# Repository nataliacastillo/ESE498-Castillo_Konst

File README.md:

# ESE498-Castillo_Konst
Capstone Project

This is the GitHub page for the 2021 ESE Capstone Design Project conducted by Natalia Castillo and Meagan Konst.<br/>
This project was titled "General Purpose Raspberry Pi HAT".<br/>
The report for this project can be found here: https://docs.google.com/document/d/1kZzHBrRYgLwNy8D9SOFyj6g7AGgq-kcxrAEOaCpLlvI/edit?usp=sharing<br/>
The final presentation slides can be found here: https://docs.google.com/presentation/d/1hZ809Xozr-wZa8N5Z7yGZ-oRJfP1h2XjGNVi-NlqP-0/edit?usp=sharing<br/>
The corresponding website can be found here: sites.wustl.edu/picap2021/<br/>

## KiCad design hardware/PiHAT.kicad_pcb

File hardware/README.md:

This section includes all of the KiCAD files for our PCB.

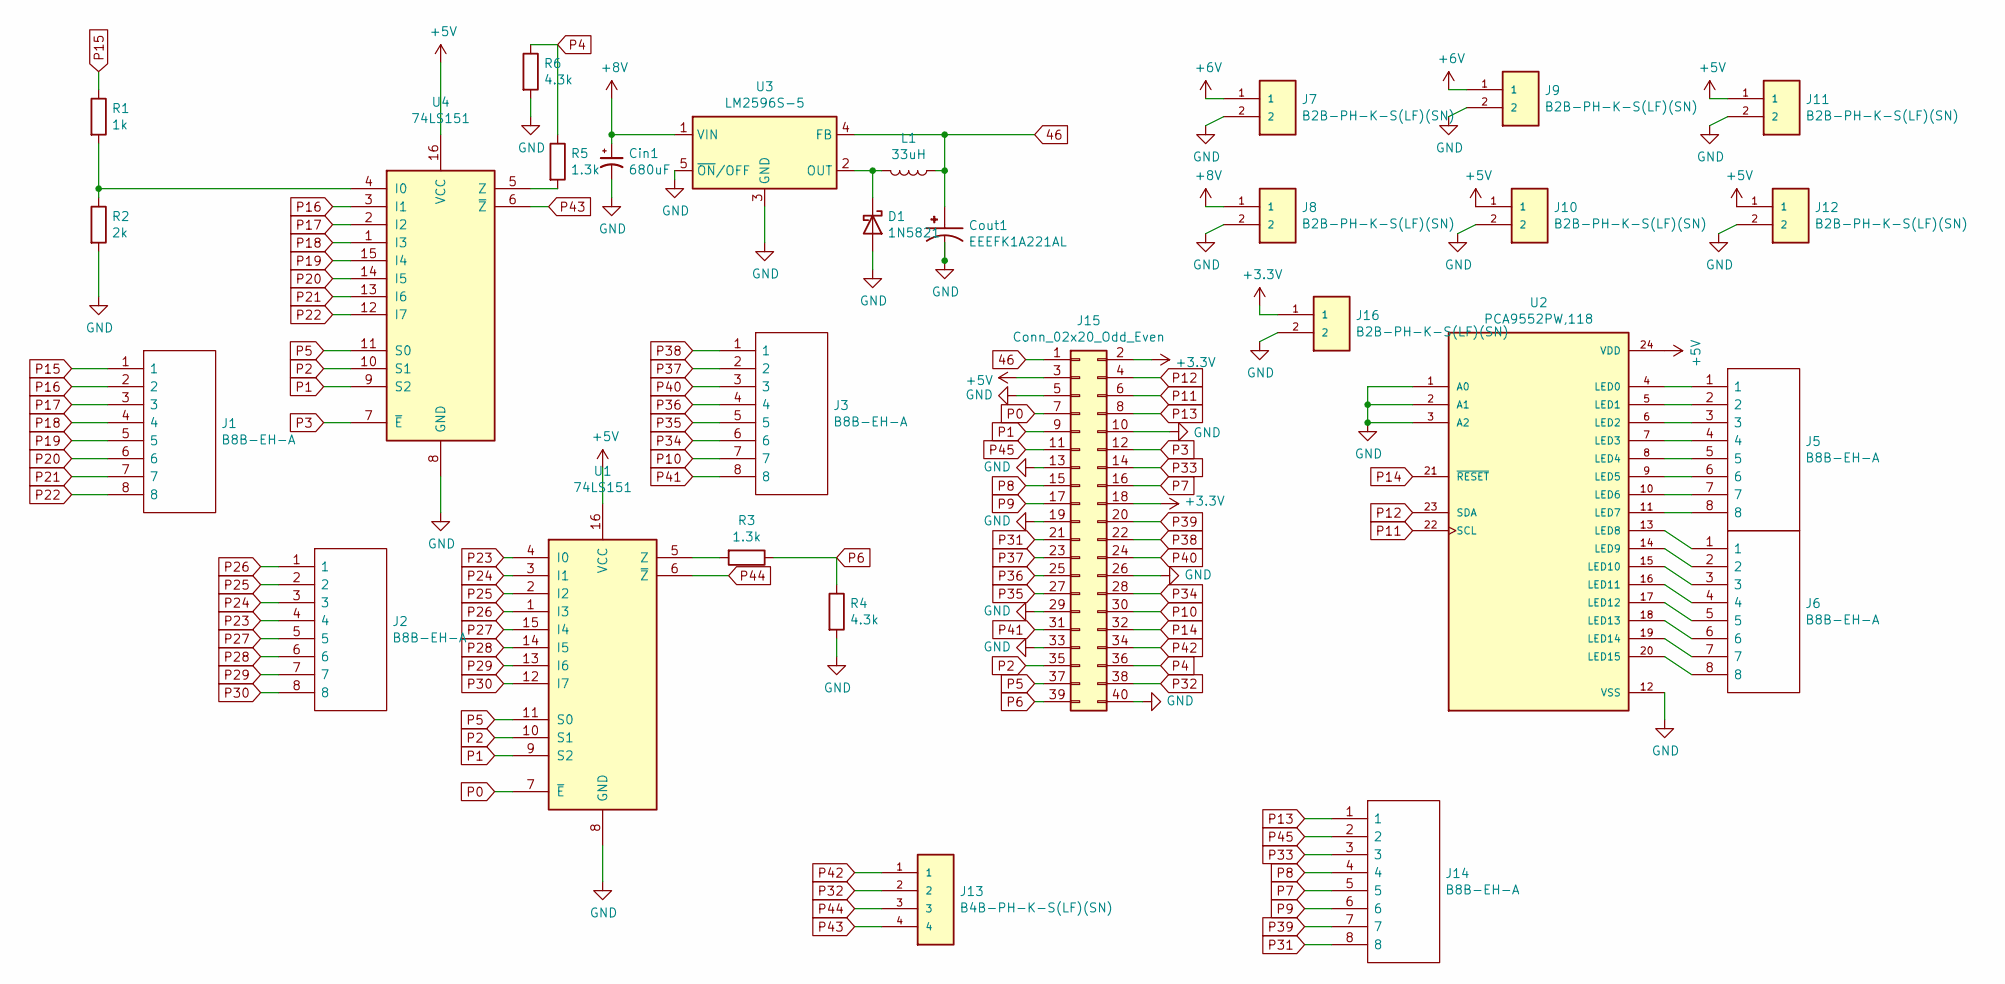
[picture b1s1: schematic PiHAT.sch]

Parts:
Cin1: 680uF; CP_Elec_10x10.5
Cout1: EEEFK1A221AL; CAP_EEEFK1A221AL; PARTREV 10-Oct-19
D1: 1N5821; D_DO-201AD_P15.24mm_Horizontal
J1, J2, J3, J5, J6, J14: B8B-EH-A; SHDR8W64P0X250_1X8_2250X380X600P; Manufacturer_Part_Number B8B-EH-A
J7, J8, J9, J10, J11, J12, J16: B2B-PH-K-S(LF)(SN); JST_B2B-PH-K-S(LF)(SN); PARTREV N/A; DIGI-KEY_PART_NUMBER 455-1704-ND
J13: B4B-PH-K-S(LF)(SN); JST_B4B-PH-K-S(LF)(SN)
J15: Conn_02x20_Odd_Even; Pin_Header_Straight_2x20
L1: 33uH; L_12x12mm_H8mm
R1: 1k; R_0402_1005Metric
R2: 2k; R_0402_1005Metric
R3, R5: 1.3k; R_0402_1005Metric
R4, R6: 4.3k; R_0402_1005Metric
U1, U4: 74LS151; SOIC127P600X175-16N
U2: PCA9552PW,118; SOP65P640X110-24N; PARTREV 05
U3: LM2596S-5; TO-263-5_TabPin3

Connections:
46: Cout1.1, J15.1, L1.1, U3.4 (FB)
+3V3: J15.2, J15.18, J16.1
+5V: J10.1, J11.1, J12.1, J15.3, U1.16 (VCC), U2.24 (VDD), U4.16 (VCC)
+6V: J7.1, J9.1
+8V: Cin1.1, J8.1, U3.1 (VIN)
GND: Cin1.2, Cout1.2, D1.2 (A), J7.2, J8.2, J9.2, J10.2, J11.2, J12.2, J15.5, J15.10, J15.13, J15.19, J15.26, J15.29, J15.33, J15.40, J16.2, R2.2, R4.2, R6.2, U1.8 (GND), U2.1 (A0), U2.2 (A1), U2.3 (A2), U2.12 (VSS), U3.3 (GND), U3.5 (~ON~/OFF), U4.8 (GND)
unnamed: D1.1 (K), L1.2, U3.2 (OUT)
unnamed: J5.1, U2.4 (LED0)
unnamed: J5.2, U2.5 (LED1)
unnamed: J5.3, U2.6 (LED2)
unnamed: J5.4, U2.7 (LED3)
unnamed: J5.5, U2.8 (LED4)
unnamed: J5.6, U2.9 (LED5)
unnamed: J5.7, U2.10 (LED6)
unnamed: J5.8, U2.11 (LED7)
unnamed: J6.1, U2.13 (LED8)
unnamed: J6.2, U2.14 (LED9)
unnamed: J6.3, U2.15 (LED10)
unnamed: J6.4, U2.16 (LED11)
unnamed: J6.5, U2.17 (LED12)
unnamed: J6.6, U2.18 (LED13)
unnamed: J6.7, U2.19 (LED14)
unnamed: J6.8, U2.20 (LED15)
unnamed: R1.2, R2.1, U4.4 (I0)
unnamed: R3.2, U1.5 (Z)
unnamed: R5.2, U4.5 (Z)
P0: J15.7, U1.7 (~E)
P1: J15.9, U1.9 (S2), U4.9 (S2)
P2: J15.35, U1.10 (S1), U4.10 (S1)
P3: J15.12, U4.7 (~E)
P4: J15.36, R5.1, R6.1
P5: J15.37, U1.11 (S0), U4.11 (S0)
P6: J15.39, R3.1, R4.1
P7: J14.5, J15.16
P8: J14.4, J15.15
P9: J14.6, J15.17
P10: J3.7, J15.30
P11: J15.6, U2.22 (SCL)
P12: J15.4, U2.23 (SDA)
P13: J14.1, J15.8
P14: J15.32, U2.21 (~RESET)
P15: J1.1, R1.1
P16: J1.2, U4.3 (I1)
P17: J1.3, U4.2 (I2)
P18: J1.4, U4.1 (I3)
P19: J1.5, U4.15 (I4)
P20: J1.6, U4.14 (I5)
P21: J1.7, U4.13 (I6)
P22: J1.8, U4.12 (I7)
P23: J2.4, U1.4 (I0)
P24: J2.3, U1.3 (I1)
P25: J2.2, U1.2 (I2)
P26: J2.1, U1.1 (I3)
P27: J2.5, U1.15 (I4)
P28: J2.6, U1.14 (I5)
P29: J2.7, U1.13 (I6)
P30: J2.8, U1.12 (I7)
P31: J14.8, J15.21
P32: J13.2, J15.38
P33: J14.3, J15.14
P34: J3.6, J15.28
P35: J3.5, J15.27
P36: J3.4, J15.25
P37: J3.2, J15.23
P38: J3.1, J15.22
P39: J14.7, J15.20
P40: J3.3, J15.24
P41: J3.8, J15.31
P42: J13.1, J15.34
P43: J13.4, U4.6 (~Z)
P44: J13.3, U1.6 (~Z)
P45: J14.2, J15.11

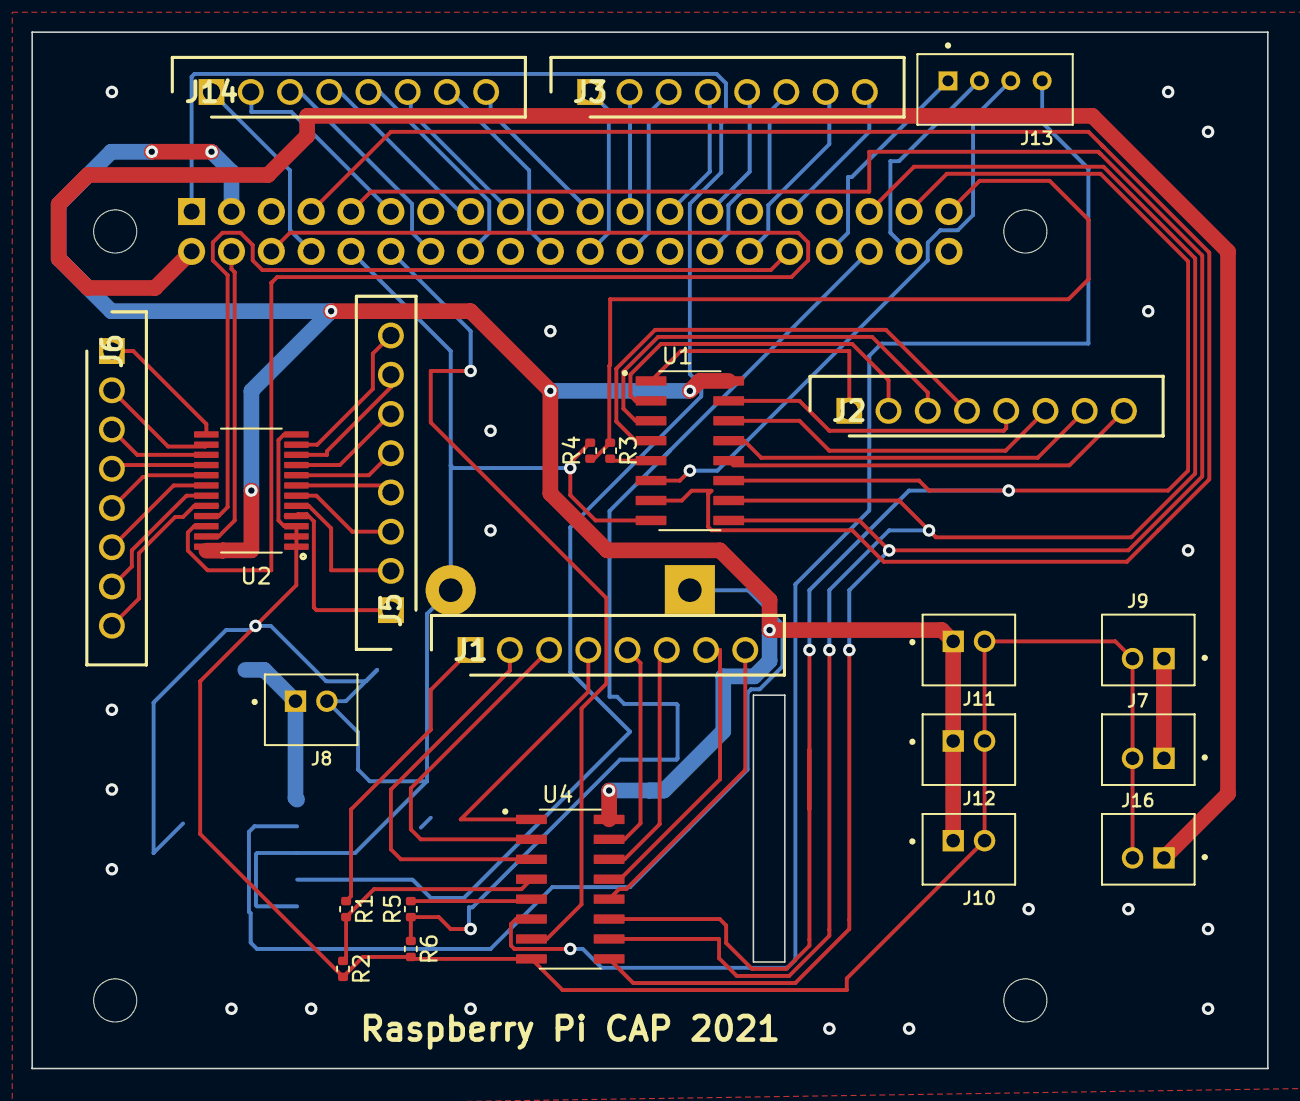
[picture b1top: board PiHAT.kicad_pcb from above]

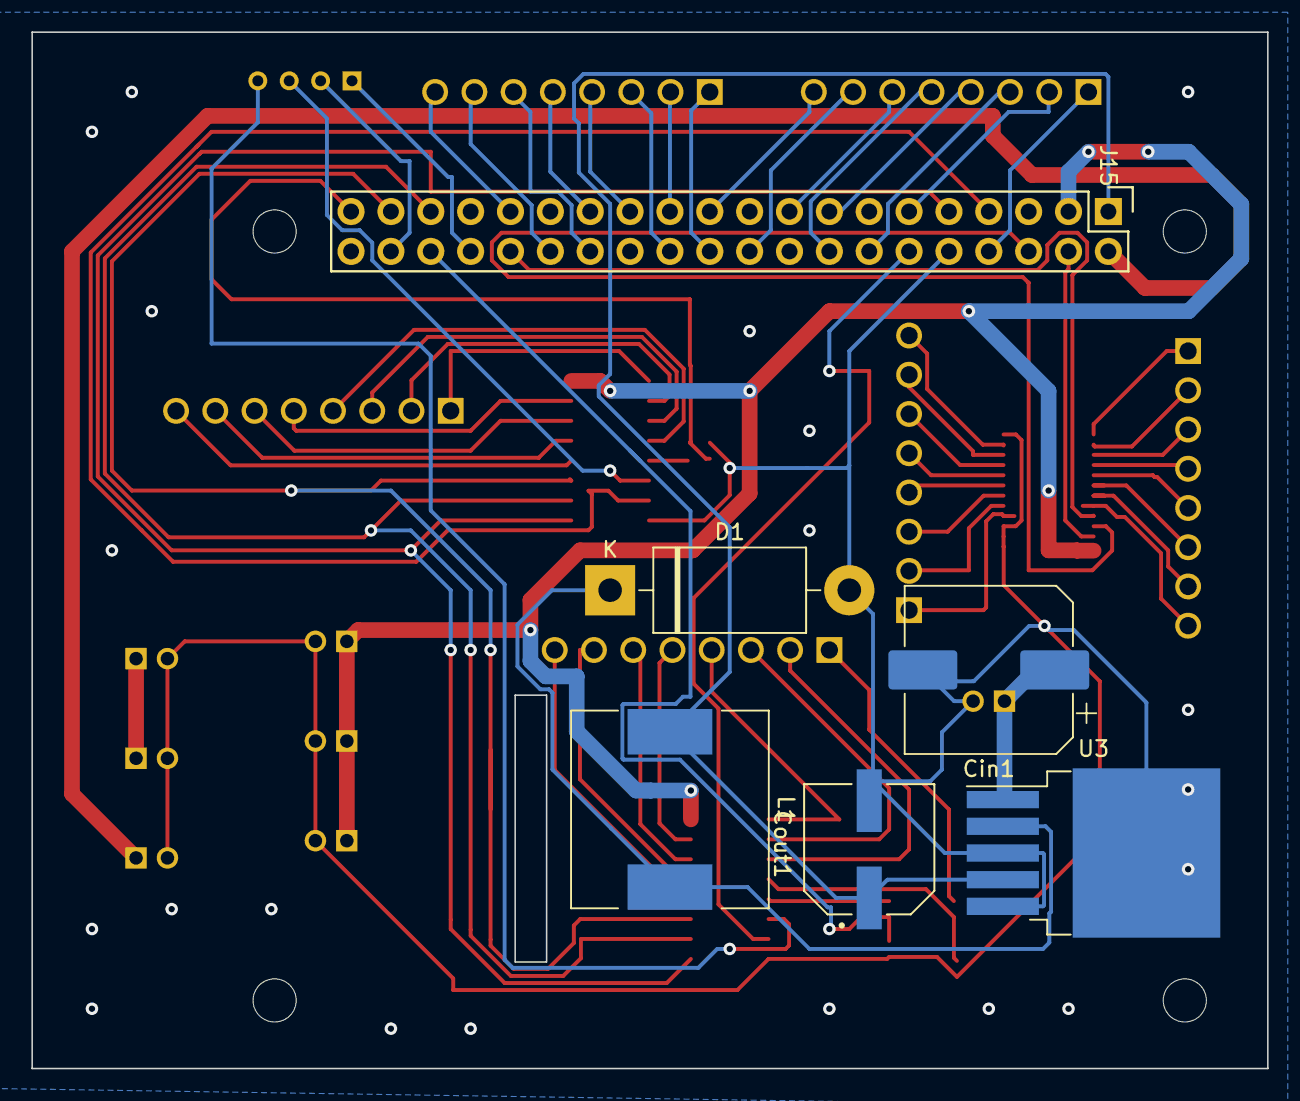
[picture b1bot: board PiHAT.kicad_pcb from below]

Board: 2 copper layers, 78.7 x 66.0 mm, 29 parts (6 on the bottom side), 72 nets.

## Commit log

2021-10-19 Add files via upload
    Rough draft of PiHAT schematic
2021-10-26 Create DW COMMENT
2021-12-17 Rename PiHAT-cache.lib to hardware/PiHAT-cache.lib
2021-12-17 Rename PiHAT.kicad_pcb to hardware/PiHAT.kicad_pcb
2021-12-17 Rename PiHAT.kicad_pcb-bak to hardware/PiHAT.kicad_pcb-bak
2021-12-17 Rename PiHAT.net to hardware/PiHAT.net
2021-12-17 Rename PiHAT.pro to hardware/PiHAT.pro
2021-12-17 Rename PiHAT.sch to hardware/PiHAT.sch
2021-12-17 Rename PiHAT.sch-bak to hardware/PiHAT.sch-bak
